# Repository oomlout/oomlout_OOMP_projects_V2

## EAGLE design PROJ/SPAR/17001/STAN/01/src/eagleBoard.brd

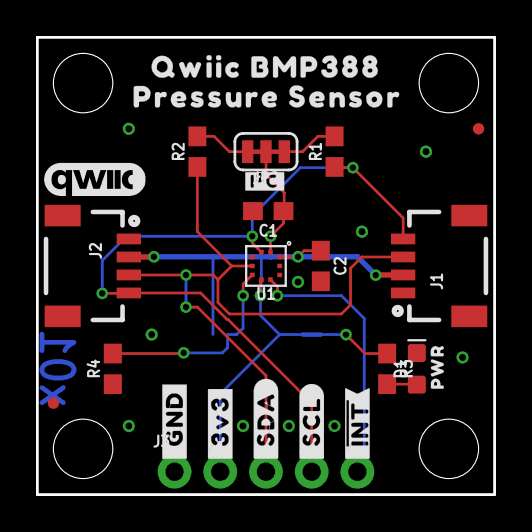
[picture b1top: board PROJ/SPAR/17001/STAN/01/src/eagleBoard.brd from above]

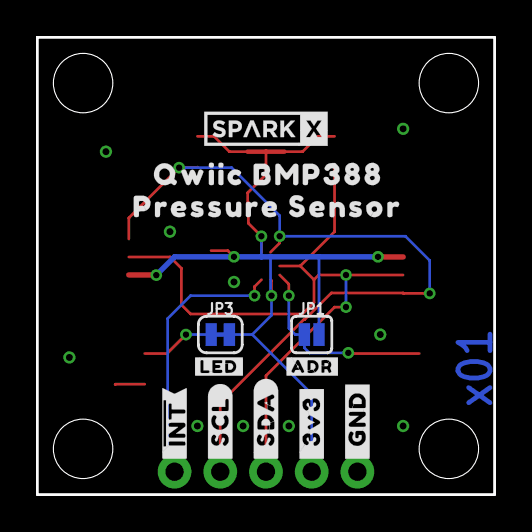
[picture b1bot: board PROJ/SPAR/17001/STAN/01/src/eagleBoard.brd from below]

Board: 2 copper layers, 25.4 x 25.4 mm, 38 parts (12 on the bottom side), 10 nets.

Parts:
A1: QWIIC_BOARD_OUTLINEH; QWIIC_BOARD_MOUNT_HOLES
C1, C2: 0.1uF; 0603
D1: RED; LED-0603
FD1, FD2: FIDUCIALUFIDUCIAL; FIDUCIAL-MICRO
FRAME1: FRAME-LETTERNO_PACKAGE; DUMMY
J1, J2: 1X04_1MM_RA
J3: 1X05_NO_SILK
JP1: SMT-JUMPER_2_NO_SILK
JP2: SMT-JUMPER_3_2-NC_TRACE_SILK
JP3: SMT-JUMPER_2_NC_TRACE_SILK
R1, R2: 2.2k; 0603
R3: 1k; 0603
R4: 10k; 0603
U1: BMP388BMP388; LGA-10(2X2)
U$1, U$13: #_GND#3889
U$2, U$12: #_3V3#3890
U$3, U$11: #_SDA#3891
U$4, U$10: #_SCL#3892
U$5, U$9: #_#INT##3893
U$6: #I�C#1
U$7: #ADR#2
U$8: #LED#0
U$14, U$17: QWIIC_BMP3888
U$15, U$18: PRESSURE_SENSOR9
U$16: QWIIC_COPYRIGHT_SMALL
U$19: SPARKX-SMALL
U$20: PWR0

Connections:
3.3V: C1.1, C2.1, J1.2, J2.2, J3.2, JP1.2, JP2.2, JP3.2, U1.1, U1.6, U1.10
ADR: JP1.1, R4.2, U1.5
GND: C1.2, C2.2, D1.C, J1.1, J2.1, J3.1, R4.1, U1.3, U1.8, U1.9
INT: J3.5, U1.7
unnamed: JP2.3, R2.2
unnamed: JP2.1, R1.2
unnamed: JP3.1, R3.1
unnamed: D1.A, R3.2
SCL: J1.4, J2.4, J3.4, R1.1, U1.2
SDA: J1.3, J2.3, J3.3, R2.1, U1.4

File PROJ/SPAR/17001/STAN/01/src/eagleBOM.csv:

"Part";"Value";"Device";"Package";"Description";"DESIGNER";"PROD_ID";"VALUE";"VERSION";
"A1";"QWIIC_BOARD_OUTLINEH";"QWIIC_BOARD_OUTLINEH";"QWIIC_BOARD_MOUNT_HOLES";"Standard Outline of a Qwiic Board. Good for defining a spot on shields and board areas in which to mount a Qwiic Board.";"";"";"";"";
"C1";"0.1uF";"0.1UF-0603-25V-(+80/-20%)";"0603";"0.1µF ceramic capacitors";"";"CAP-00810";"0.1uF";"";
"C2";"0.1uF";"0.1UF-0603-25V-(+80/-20%)";"0603";"0.1µF ceramic capacitors";"";"CAP-00810";"0.1uF";"";
"D1";"RED";"LED-RED0603";"LED-0603";"Red SMD LED";"";"DIO-00819";"RED";"";
"FD1";"FIDUCIALUFIDUCIAL";"FIDUCIALUFIDUCIAL";"FIDUCIAL-MICRO";"Fiducial Alignment Points";"";"";"";"";
"FD2";"FIDUCIALUFIDUCIAL";"FIDUCIALUFIDUCIAL";"FIDUCIAL-MICRO";"Fiducial Alignment Points";"";"";"";"";
"FRAME1";"FRAME-LETTERNO_PACKAGE";"FRAME-LETTERNO_PACKAGE";"DUMMY";"Schematic Frame - Letter";"Nobody";"";"";"v01";
"J1";"";"QWIIC_CONNECTORJS-1MM";"1X04_1MM_RA";"SparkFun I2C Standard Qwiic Connector";"";"";"";"";
"J2";"";"QWIIC_CONNECTORJS-1MM";"1X04_1MM_RA";"SparkFun I2C Standard Qwiic Connector";"";"";"";"";
"J3";"";"CONN_05NO_SILK";"1X05_NO_SILK";"Multi connection point. Often used as Generic Header-pin footprint for 0.1 inch spaced/style header connections";"";"";"";"";
"JP1";"";"JUMPER-SMT_2_NO_SILK";"SMT-JUMPER_2_NO_SILK";"Normally open jumper";"";"";"";"";
"JP2";"";"JUMPER-SMT_3_2-NC_TRACE_SILK";"SMT-JUMPER_3_2-NC_TRACE_SILK";"Normally closed trace jumper (2 of 2 connections)";"";"";"";"";
"JP3";"";"JUMPER-SMT_2_NC_TRACE_SILK";"SMT-JUMPER_2_NC_TRACE_SILK";"Normally closed trace jumper";"";"";"";"";
"R1";"2.2k";"2.2KOHM-0603-1/10W-1%";"0603";"2.2kΩ resistor";"";"RES-08272";"2.2k";"";
"R2";"2.2k";"2.2KOHM-0603-1/10W-1%";"0603";"2.2kΩ resistor";"";"RES-08272";"2.2k";"";
"R3";"1k";"1KOHM-0603-1/10W-1%";"0603";"1kΩ resistor";"";"RES-07856";"1k";"";
"R4";"10k";"10KOHM-0603-1/10W-1%";"0603";"10kΩ resistor";"";"RES-00824";"10k";"";
"U1";"BMP388BMP388";"BMP388BMP388";"LGA-10(2X2)";"Bosch BMP3388 Pressure Sensor";"";"IC-14045";"";"";

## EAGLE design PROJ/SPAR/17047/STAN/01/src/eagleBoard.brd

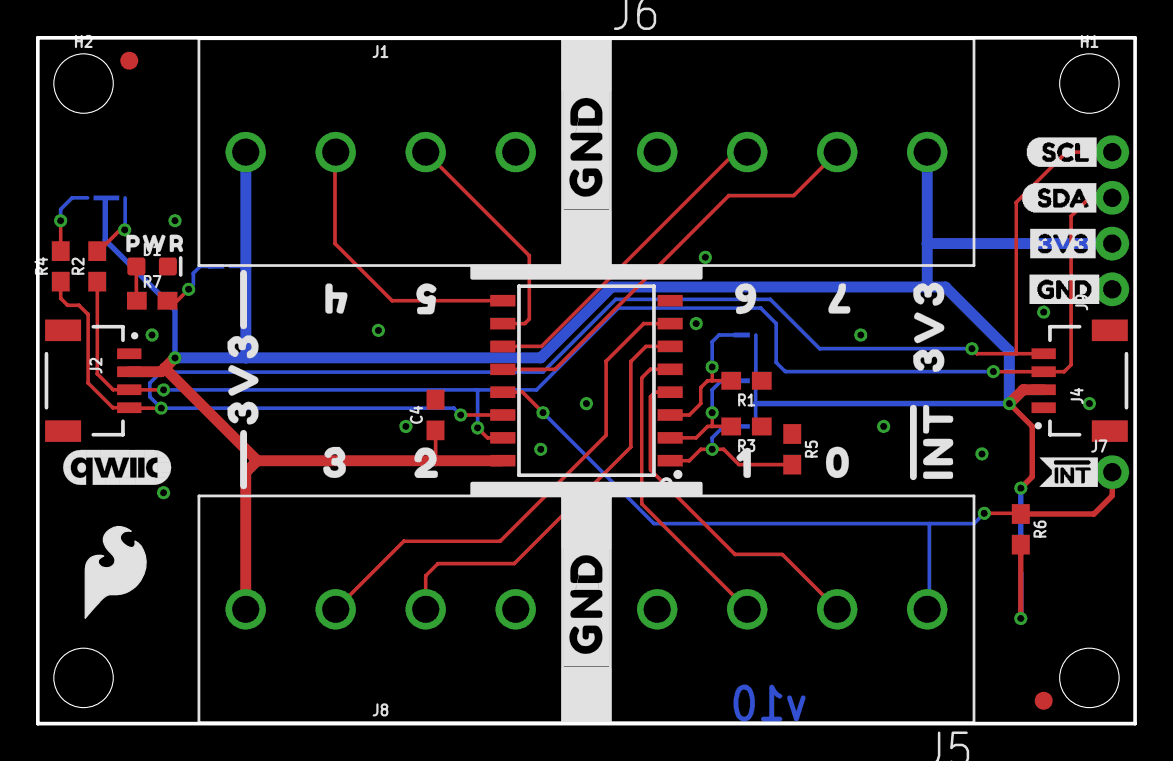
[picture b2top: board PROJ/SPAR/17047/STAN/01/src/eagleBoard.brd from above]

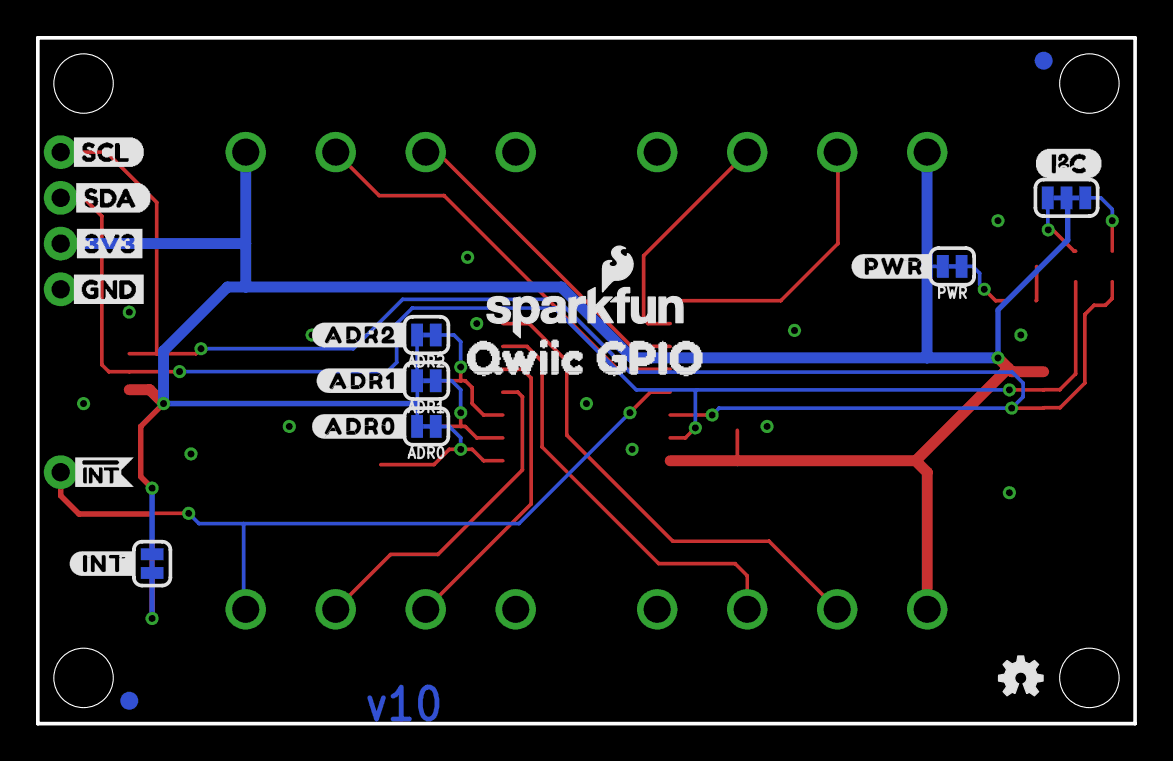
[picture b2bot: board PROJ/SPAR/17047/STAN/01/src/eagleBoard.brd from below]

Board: 2 copper layers, 61.0 x 38.1 mm, 69 parts (22 on the bottom side), 21 nets.

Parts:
ADR0, ADR1, ADR2: JUMPER-SMT_2_NC_TRACE_SILK; SMT-JUMPER_2_NC_TRACE_SILK
C4: 0.1uF; 0603
D1: RED; LED-0603
FD1, FD2: FIDUCIAL1X2; FIDUCIAL-1X2
FRAME1: FRAME-LETTER; CREATIVE_COMMONS
H1, H2: STAND-OFF
I2C: JUMPER-SMT_3_2-NC_TRACE_SILK; SMT-JUMPER_3_2-NC_TRACE_SILK
INT: JUMPER-SMT_2_NC_TRACE_SILK; SMT-JUMPER_2_NC_TRACE_SILK
J1, J5, J6, J8: LATCHTERMINAL-5MM-4
J2, J4: QWIIC; JST04_1MM_RA
J7: 1X01_NO_SILK
J9: 1X04_NO_SILK
JP2, JP6: FIDUCIAL1X2; FIDUCIAL-1X2
JP3, JP4: STAND-OFF
LOGO1: OSHW-LOGOMINI; OSHW-LOGO-MINI
LOGO2: REVISION
LOGO3: SFE_LOGO_NAME_FLAME.1_INCH; SFE_LOGO_NAME_FLAME_.1
LOGO4: SFE_LOGO_FLAME.2_INCH; SFE_LOGO_FLAME_.2
PWR: JUMPER-SMT_2_NC_TRACE_SILK; SMT-JUMPER_2_NC_TRACE_SILK
R1, R2, R3, R4, R5: 2.2k; 0603
R6: 10k; 0603
R7: 1k; 0603
U3: TCA9534; 16SOIC
U$1: I2C
U$2: 20
U$3, U$26: 3V33
U$4: 30
U$5: #ADR1#0
U$6: 10
U$7, U$25: GND4
U$8: QWIIC_GPIO7
U$9: SCL6
U$10: SDA5
U$11: #ADR2#0
U$12: #INT#0
U$13, U$22, U$29: #INT0
U$14: 00
U$15: #ADR0#0
U$21: QWIIC_6MM
U$23: SCL0
U$24: SDA1
U$30, U$31: 3V30
U$32: 40
U$33: 50
U$34: PWR0
U$35: 60
U$37: 70
U$38, U$40: #GND#0
U$39: #PWR#0

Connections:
3.3V: ADR0.2, ADR1.2, ADR2.2, C4.1, I2C.2, INT.2, J1.1, J2.2, J4.2, J6.4, J8.4, J9.2, PWR.2, U3.16
!INT: J5.1, J7.1, R6.1, U3.13
ADR0: ADR0.1, R5.2, U3.1
ADR1: ADR1.1, R3.2, U3.2
ADR2: ADR2.1, R1.2, U3.3
GND: C4.2, D1.C, J1.4, J2.1, J4.1, J5.4, J6.1, J8.1, J9.1, R1.1, R3.1, R5.1, U3.8
unnamed: INT.1, R6.2
unnamed: D1.A, R7.1
unnamed: PWR.1, R7.2
P0: J5.2, U3.4
P1: J5.3, U3.5
P2: J8.2, U3.6
P3: J8.3, U3.7
P4: J1.2, U3.9
P5: J1.3, U3.10
P6: J6.2, U3.11
P7: J6.3, U3.12
SCL: J2.4, J4.4, J9.4, R4.1, U3.14
SCL_PU1: I2C.1, R2.2
SDA: J2.3, J4.3, J9.3, R2.1, U3.15
SDA_PU1: I2C.3, R4.2

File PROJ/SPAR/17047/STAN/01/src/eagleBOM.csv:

"Part";"Value";"Device";"Package";"Description";"DESIGNER";"PROD_ID";"REV";"STOREFRONT_SKU";"VALUE";
"ADR0";"JUMPER-SMT_2_NC_TRACE_SILK";"JUMPER-SMT_2_NC_TRACE_SILK";"SMT-JUMPER_2_NC_TRACE_SILK";"Normally closed trace jumper";"";"";"";"";"";
"ADR1";"JUMPER-SMT_2_NC_TRACE_SILK";"JUMPER-SMT_2_NC_TRACE_SILK";"SMT-JUMPER_2_NC_TRACE_SILK";"Normally closed trace jumper";"";"";"";"";"";
"ADR2";"JUMPER-SMT_2_NC_TRACE_SILK";"JUMPER-SMT_2_NC_TRACE_SILK";"SMT-JUMPER_2_NC_TRACE_SILK";"Normally closed trace jumper";"";"";"";"";"";
"C4";"0.1uF";"0.1UF-0603-25V-(+80/-20%)";"0603";"0.1µF ceramic capacitors";"";"CAP-00810";"";"";"0.1uF";
"D1";"RED";"LED-RED0603";"LED-0603";"Red SMD LED";"";"DIO-00819";"";"";"RED";
"FD1";"FIDUCIAL1X2";"FIDUCIAL1X2";"FIDUCIAL-1X2";"Fiducial Alignment Points";"";"";"";"";"";
"FD2";"FIDUCIAL1X2";"FIDUCIAL1X2";"FIDUCIAL-1X2";"Fiducial Alignment Points";"";"";"";"";"";
"FRAME1";"FRAME-LETTER";"FRAME-LETTER";"CREATIVE_COMMONS";"Schematic Frame - Letter";"";"";"";"";"";
"H1";"STAND-OFF";"STAND-OFF";"STAND-OFF";"Stand Off";"";"";"";"";"";
"H2";"STAND-OFF";"STAND-OFF";"STAND-OFF";"Stand Off";"";"";"";"";"";
"I2C";"JUMPER-SMT_3_2-NC_TRACE_SILK";"JUMPER-SMT_3_2-NC_TRACE_SILK";"SMT-JUMPER_3_2-NC_TRACE_SILK";"Normally closed trace jumper (2 of 2 connections)";"";"";"";"";"";
"INT";"JUMPER-SMT_2_NC_TRACE_SILK";"JUMPER-SMT_2_NC_TRACE_SILK";"SMT-JUMPER_2_NC_TRACE_SILK";"Normally closed trace jumper";"";"";"";"";"";
"J1";"";"CONN_04LATCH";"LATCHTERMINAL-5MM-4";"Multi connection point. Often used as Generic Header-pin footprint for 0.1 inch spaced/style header connections";"";"CON-14722";"";"PRT-15900";"";
"J2";"QWIIC";"QWIIC_CONNECTORJS-1MM";"JST04_1MM_RA";"SparkFun I2C Standard Qwiic Connector";"";"CONN-13694";"";"";"QWIIC_RIGHT_ANGLE";
"J4";"QWIIC";"QWIIC_CONNECTORJS-1MM";"JST04_1MM_RA";"SparkFun I2C Standard Qwiic Connector";"";"CONN-13694";"";"";"QWIIC_RIGHT_ANGLE";
"J5";"";"CONN_04LATCH";"LATCHTERMINAL-5MM-4";"Multi connection point. Often used as Generic Header-pin footprint for 0.1 inch spaced/style header connections";"";"CON-14722";"";"PRT-15900";"";
"J6";"";"CONN_04LATCH";"LATCHTERMINAL-5MM-4";"Multi connection point. Often used as Generic Header-pin footprint for 0.1 inch spaced/style header connections";"";"CON-14722";"";"PRT-15900";"";
"J7";"";"CONN_01PTH_NO_SILK_YES_STOP";"1X01_NO_SILK";"Single connection point. Often used as Generic Header-pin footprint for 0.1 inch spaced/style header connections";"";"";"";"";"";
"J8";"";"CONN_04LATCH";"LATCHTERMINAL-5MM-4";"Multi connection point. Often used as Generic Header-pin footprint for 0.1 inch spaced/style header connections";"";"CON-14722";"";"PRT-15900";"";
"J9";"";"CONN_041X04_NO_SILK";"1X04_NO_SILK";"Multi connection point. Often used as Generic Header-pin footprint for 0.1 inch spaced/style header connections";"";"CONN-09696";"";"";"";
"JP2";"FIDUCIAL1X2";"FIDUCIAL1X2";"FIDUCIAL-1X2";"Fiducial Alignment Points";"";"";"";"";"";
"JP3";"STAND-OFF";"STAND-OFF";"STAND-OFF";"Stand Off";"";"";"";"";"";
"JP4";"STAND-OFF";"STAND-OFF";"STAND-OFF";"Stand Off";"";"";"";"";"";
"JP6";"FIDUCIAL1X2";"FIDUCIAL1X2";"FIDUCIAL-1X2";"Fiducial Alignment Points";"";"";"";"";"";
"LOGO1";"OSHW-LOGOMINI";"OSHW-LOGOMINI";"OSHW-LOGO-MINI";"Open-Source Hardware (OSHW) Logo";"";"";"";"";"";
"LOGO2";"REVISION";"REVISION";"REVISION";""Revision By" Text";"";"";"";"";"";
"LOGO3";"SFE_LOGO_NAME_FLAME.1_INCH";"SFE_LOGO_NAME_FLAME.1_INCH";"SFE_LOGO_NAME_FLAME_.1";"SparkFun Font Logo w/ Flame";"";"";"";"";"";
"LOGO4";"SFE_LOGO_FLAME.2_INCH";"SFE_LOGO_FLAME.2_INCH";"SFE_LOGO_FLAME_.2";"SparkFun Flame Logo";"";"";"";"";"";
"PWR";"JUMPER-SMT_2_NC_TRACE_SILK";"JUMPER-SMT_2_NC_TRACE_SILK";"SMT-JUMPER_2_NC_TRACE_SILK";"Normally closed trace jumper";"";"";"";"";"";
"R1";"2.2k";"2.2KOHM-0603-1/10W-1%";"0603";"2.2kΩ resistor";"";"RES-08272";"";"";"2.2k";
"R2";"2.2k";"2.2KOHM-0603-1/10W-1%";"0603";"2.2kΩ resistor";"";"RES-08272";"";"";"2.2k";
"R3";"2.2k";"2.2KOHM-0603-1/10W-1%";"0603";"2.2kΩ resistor";"";"RES-08272";"";"";"2.2k";
"R4";"2.2k";"2.2KOHM-0603-1/10W-1%";"0603";"2.2kΩ resistor";"";"RES-08272";"";"";"2.2k";
"R5";"2.2k";"2.2KOHM-0603-1/10W-1%";"0603";"2.2kΩ resistor";"";"RES-08272";"";"";"2.2k";
"R6";"10k";"10KOHM-0603-1/10W-1%";"0603";"10kΩ resistor";"";"RES-00824";"";"";"10k";
"R7";"1k";"1KOHM-0603-1/10W-1%";"0603";"1kΩ resistor";"";"RES-07856";"";"";"1k";
"U3";"TCA9534";"TCA9534U";"16SOIC";"Texas Instruments TCA9534 I2C -> GPIO Expander";"";"IC-14889";"";"";"TCA9534";

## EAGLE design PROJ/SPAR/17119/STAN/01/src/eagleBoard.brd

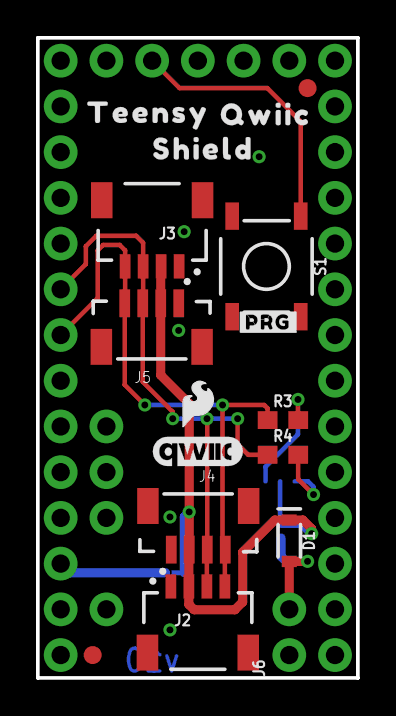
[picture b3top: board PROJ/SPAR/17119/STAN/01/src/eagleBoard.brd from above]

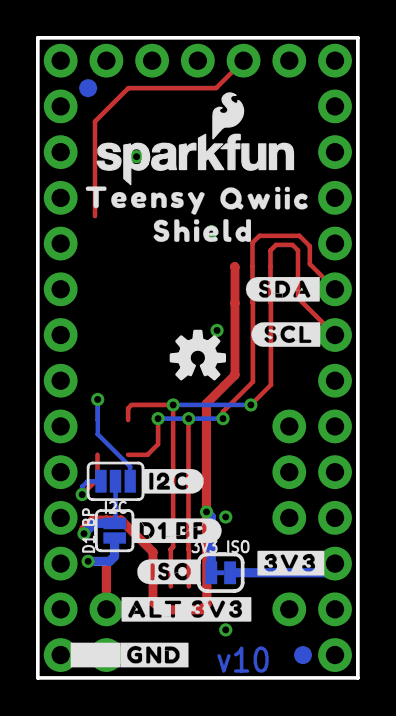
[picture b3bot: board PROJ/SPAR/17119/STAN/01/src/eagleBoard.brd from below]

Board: 2 copper layers, 17.8 x 35.6 mm, 38 parts (18 on the bottom side), 9 nets.

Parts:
3V3_ISO: SMT-JUMPER_2_NC_TRACE_SILK
D1: 3A/10V/280mV; SOD-323
D1_BP: SMT-JUMPER_2_NO_SILK
FD1, FD2, FD3, FD4: FIDUCIAL1X2; FIDUCIAL-1X2
FRAME1: FRAME-LETTER; CREATIVE_COMMONS
I2C: JUMPER-SMT_3_NO_SILK; SMT-JUMPER_3_NO_SILK
J1: TEENSY; TEENSY_NOSILK
J2, J3: QWIIC_RA; JST04_1MM_RA
J4, J5: QWIIC_Vertical; JST04_1MM_VERT
J6: ALT PWR; 1X02_NO_SILK
LOGO1: SFE_LOGO_NAME_FLAME.1_INCH; SFE_LOGO_NAME_FLAME_.1
LOGO2: SFE_LOGO_FLAME.1_INCH; SFE_LOGO_FLAME_.1
LOGO3: OSHW-LOGOS; OSHW-LOGO-S
LOGO4: QWIIC_LOGO_5MM; QWIIC_5MM
R3, R4: 4.7k; 0603
S1: SMD_5.2MM; TACTILE_SWITCH_SMD_5.2MM
U$1: #I2C#0
U$2, U$13: TEENSY0
U$3: 3V36
U$4: #D1_BP#0
U$5: #ALT_3V3#0
U$6: #PRG#0
U$7: #GND#0
U$8, U$12: SHIELD0
U$9, U$11: QWIIC0
U$10: #ISO#0
U$15: #3V3#0
U$18: #SDA#0
U$19: #SCL#0

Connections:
3.3V: 3V3_ISO.1, D1.C, D1_BP.2, I2C.2, J2.2, J3.2, J4.2, J5.2
GND: J1.AGND, J1.GND, J1.GND1, J2.1, J3.1, J4.1, J5.1, J6.1, S1.3
unnamed: I2C.3, R4.2
unnamed: I2C.1, R3.2
unnamed: 3V3_ISO.2, J1.3V
unnamed: D1.A, D1_BP.1, J6.2
unnamed: J1.PROG, S1.1
SCL: J1.19, J2.4, J3.4, J4.4, J5.4, R3.1
SDA: J1.18, J2.3, J3.3, J4.3, J5.3, R4.1

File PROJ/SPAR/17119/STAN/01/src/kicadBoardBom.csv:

"Id";"Designator";"Package";"Quantity";"Designation";"Supplier and ref";
1;"LOGO2";"SFE_LOGO_FLAME_.1";1;"SFE_LOGO_FLAME.1_INCH";;;
2;"J4,J5";"JST04_1MM_VERT";2;"QWIIC_Vertical";;;
3;"U$9,U$11";"QWIIC0";2;"";;;
4;"U$13,U$2";"TEENSY0";2;"";;;
5;"U$6";"#PRG#0";1;"";;;
6;"J1";"TEENSY_NOSILK";1;"TEENSY";;;
7;"FRAME1";"CREATIVE_COMMONS";1;"FRAME-LETTER";;;
8;"R4,R3";"0603";2;"4.7k";;;
9;"U$8,U$12";"SHIELD0";2;"";;;
10;"U$3";"3V36";1;"";;;
11;"D1";"SOD-323";1;"3A/10V/280mV";;;
12;"J3,J2";"JST04_1MM_RA";2;"QWIIC_RA";;;
13;"LOGO4";"QWIIC_5MM";1;"QWIIC_LOGO_5MM";;;
14;"FD3,FD1,FD2,FD4";"FIDUCIAL-1X2";4;"FIDUCIAL1X2";;;
15;"S1";"TACTILE_SWITCH_SMD_5.2MM";1;"SMD_5.2MM";;;
16;"J6";"1X02_NO_SILK";1;"ALT PWR";;;
17;"U$1";"#I2C#0";1;"";;;
18;"UNK3V3_ISO0";"SMT-JUMPER_2_NC_TRACE_SILK";1;"";;;
19;"U$7";"#GND#0";1;"";;;
20;"LOGO3";"OSHW-LOGO-S";1;"OSHW-LOGOS";;;
21;"U$10";"#ISO#0";1;"";;;
22;"D1_BP0";"SMT-JUMPER_2_NO_SILK";1;"";;;
23;"U$15";"#3V3#0";1;"";;;
24;"LOGO1";"SFE_LOGO_NAME_FLAME_.1";1;"SFE_LOGO_NAME_FLAME.1_INCH";;;
25;"U$18";"#SDA#0";1;"";;;
26;"U$5";"#ALT_3V3#0";1;"";;;
27;"U$19";"#SCL#0";1;"";;;
28;"U$4";"#D1_BP#0";1;"";;;
29;"I2C0";"SMT-JUMPER_3_NO_SILK";1;"JUMPER-SMT_3_NO_SILK";;;

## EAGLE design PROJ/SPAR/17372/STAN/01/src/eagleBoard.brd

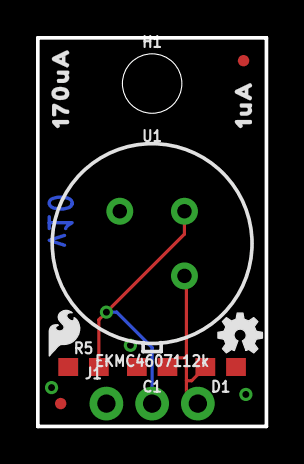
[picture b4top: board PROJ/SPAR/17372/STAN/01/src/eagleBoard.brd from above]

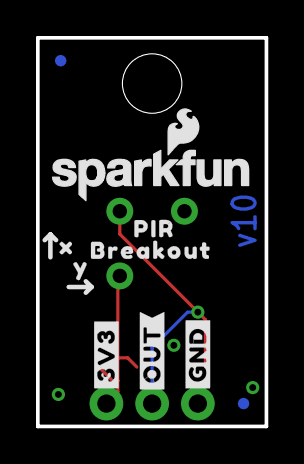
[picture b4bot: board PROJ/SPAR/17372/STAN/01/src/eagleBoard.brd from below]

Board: 2 copper layers, 12.7 x 21.6 mm, 23 parts (10 on the bottom side), 3 nets.

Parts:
C1: 0.1uF; 0603
D1: 24V; 0603
FRAME1: FRAME-LETTER; CREATIVE_COMMONS
H1: STAND-OFF
J1: 1X03_NO_SILK
JP2, JP6, JP8, JP9: FIDUCIALUFIDUCIAL; MICRO-FIDUCIAL
LOGO1: OSHW-LOGOMINI; OSHW-LOGO-MINI
LOGO3: SFE_LOGO_NAME_FLAME.1_INCH; SFE_LOGO_NAME_FLAME_.1
LOGO4: SFE_LOGO_FLAME.1_INCH; SFE_LOGO_FLAME_.1
R5: 47k; 0603
U1: EKMC4607112k; TO-3
U$1: #3V3#0
U$2: 170UA0
U$3: #GND#0
U$9: 1UA0
U$11: #OUT#0
U$12: BREAKOUT0
U$13: PIR0
U$14: X0
U$16: Y0

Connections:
3.3V: C1.1, D1.2, J1.3, U1.VDD
GND: C1.2, D1.1, J1.1, R5.1, U1.GND
PIR_OUT: J1.2, R5.2, U1.OUT

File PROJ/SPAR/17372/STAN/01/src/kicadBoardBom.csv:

"Id";"Designator";"Package";"Quantity";"Designation";"Supplier and ref";
1;"FRAME1";"CREATIVE_COMMONS";1;"FRAME-LETTER";;;
2;"R5";"0603";1;"47k";;;
3;"U$2";"170UA0";1;"";;;
4;"U$9";"1UA0";1;"";;;
5;"LOGO1";"OSHW-LOGO-MINI";1;"OSHW-LOGOMINI";;;
6;"U1";"TO-3";1;"EKMC4607112k";;;
7;"H1";"STAND-OFF";1;"STAND-OFF";;;
8;"J1";"1X03_NO_SILK";1;"";;;
9;"D1";"0603";1;"24V";;;
10;"LOGO4";"SFE_LOGO_FLAME_.1";1;"SFE_LOGO_FLAME.1_INCH";;;
11;"JP9,JP8,JP2,JP6";"MICRO-FIDUCIAL";4;"FIDUCIALUFIDUCIAL";;;
12;"C1";"0603";1;"0.1uF";;;
13;"U$11";"#OUT#0";1;"";;;
14;"U$3";"#GND#0";1;"";;;
15;"LOGO3";"SFE_LOGO_NAME_FLAME_.1";1;"SFE_LOGO_NAME_FLAME.1_INCH";;;
16;"U$12";"BREAKOUT0";1;"";;;
17;"U$13";"PIR0";1;"";;;
18;"U$1";"#3V3#0";1;"";;;
19;"U$16";"Y0";1;"";;;
20;"U$14";"X0";1;"";;;

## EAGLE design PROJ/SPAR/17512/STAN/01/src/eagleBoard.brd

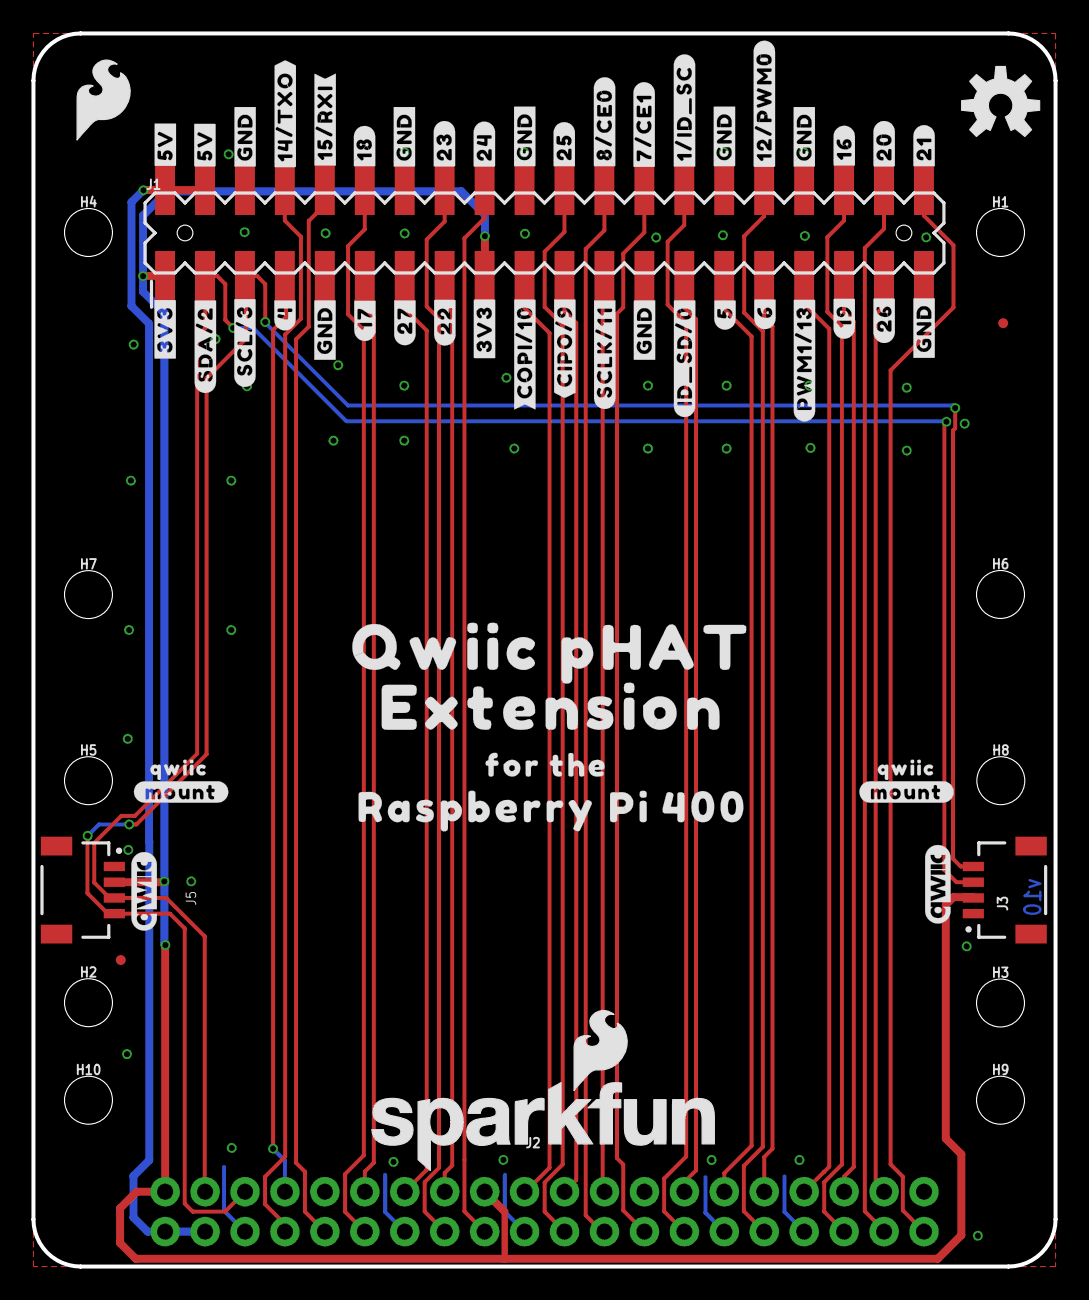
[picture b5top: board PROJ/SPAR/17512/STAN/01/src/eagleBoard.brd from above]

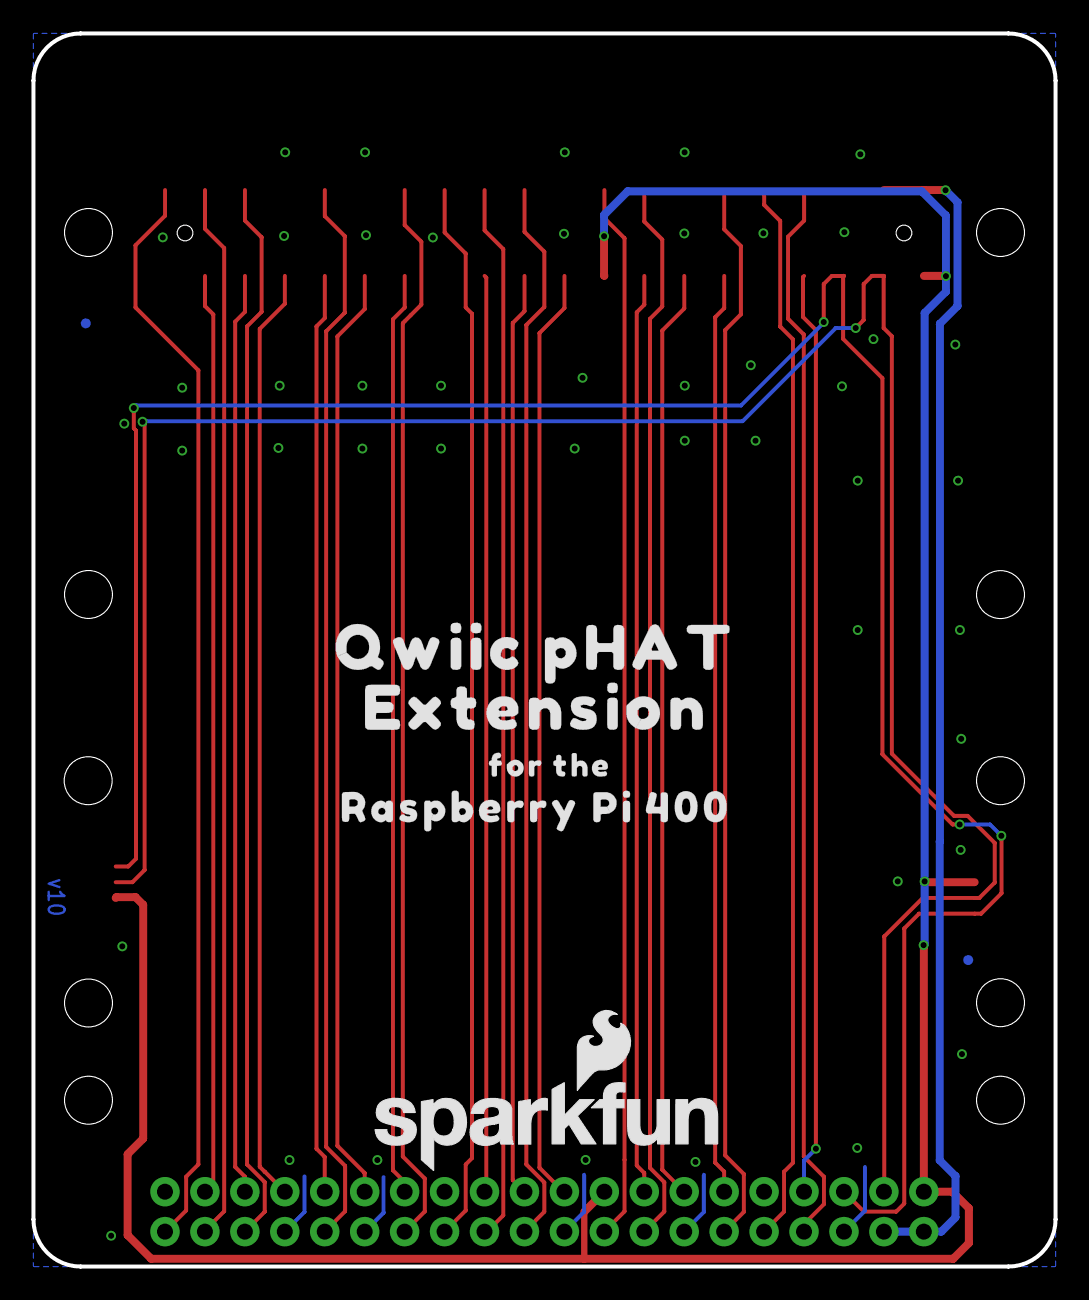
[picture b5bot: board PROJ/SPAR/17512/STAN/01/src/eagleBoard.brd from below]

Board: 2 copper layers, 65.0 x 78.4 mm, 77 parts (7 on the bottom side), 31 nets.

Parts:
FD1, FD2, FD3, FD4: FIDUCIALUFIDUCIAL; FIDUCIAL-MICRO
FRAME1: FRAME-LETTER; CREATIVE_COMMONS
H1, H2, H3, H4, H5, H6, H7, H8, H9, H10: STAND-OFFTIGHT; STAND-OFF-TIGHT
J1: RASPBERRYPI-40-PIN-GPIO_SMD_MALE; RASPBERRY_PI_HAT_40_PIN_SMD_MALE
J2: RASPBERRYPI-40-PIN-GPIO_RIGHT_ANGLE; 2X20_RIGHT_ANGLE
J3, J5: QWIIC_RIGHT_ANGLE; JST04_1MM_RA
LOGO1, LOGO4: QWIIC_LOGO_5MM; QWIIC_5MM
LOGO2, LOGO5: SFE_LOGO_NAME_FLAME.2_INCH; SFE_LOGO_NAME_FLAME_.2
LOGO3: OSHW-LOGOM; OSHW-LOGO-M
U$1: #SDA#2#4
U$2: #SCL#3#4
U$3, U$13: FOR_THE40034
U$4, U$5: #3V3#0
U$6: #4#4
U$7: #5#28
U$8, U$9: #5V#28
U$10: #6#28
U$11: #7#CE1#29
U$12: #8#CE0#29
U$14: #SCLK#11#28
U$15: #ID_SD#0#28
U$16: #12#PWM0#29
U$17: #PWM1#13#28
U$18: #14#TXO#29
U$19: #15#RXI#29
U$20: #16#29
U$21: #17#5
U$22: #18#29
U$23: #19#28
U$24: #20#29
U$25: #21#29
U$26: #22#28
U$27: #23#29
U$28: #24#29
U$29: #25#29
U$30: #26#28
U$31: #27#18
U$32, U$33, U$34, U$35, U$36, U$37, U$38, U$39: #GND#28
U$40: #1#ID_SC#29
U$51: #CIPO#9#28
U$52: #COPI#10#28
U$75, U$89: QWIIC_PHAT31
U$76, U$90: EXTENSION32
U$81: SFE_LOGO_FLAME_.2
U$82, U$83: #MOUNT#29
U$84, U$85: QWIIC30
U$86, U$91: RASPBERRY_PI_40033

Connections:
0/ID_SD: J1.27, J2.27
1/ID_SC: J1.28, J2.28
2/SDA: J1.3, J2.3, J3.3, J5.3
3.3V: J1.1, J1.17, J2.1, J2.17, J3.2, J5.2
3/SCL: J1.5, J2.5, J3.4, J5.4
5V: J1.2, J1.4, J2.2, J2.4
7/CE1: J1.26, J2.26
8/CE0: J1.24, J2.24
9/CIPO: J1.21, J2.21
10/COPI: J1.19, J2.19
11/SCLK: J1.23, J2.23
12/PWM0: J1.32, J2.32
13/PWM1: J1.33, J2.33
14/TXO: J1.8, J2.8
15/RXI: J1.10, J2.10
18/PCM_CLK: J1.12, J2.12
19/PCM_FS: J1.35, J2.35
20/PCM_DIN: J1.38, J2.38
21/PCM_DOUT: J1.40, J2.40
GND: J1.6, J1.9, J1.14, J1.20, J1.25, J1.30, J1.34, J1.39, J2.6, J2.9, J2.14, J2.20, J2.25, J2.30, J2.34, J2.39, J3.1, J5.1
GP4: J1.7, J2.7
GP5: J1.29, J2.29
GP6: J1.31, J2.31
GP16: J1.36, J2.36
GP17: J1.11, J2.11
GP22: J1.15, J2.15
GP23: J1.16, J2.16
GP24: J1.18, J2.18
GP25: J1.22, J2.22
GP26: J1.37, J2.37
GP27: J1.13, J2.13

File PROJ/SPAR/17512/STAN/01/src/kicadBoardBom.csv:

"Id";"Designator";"Package";"Quantity";"Designation";"Supplier and ref";
1;"U$10";"#6#28";1;"";;;
2;"U$35,U$33,U$34,U$37,U$39,U$38,U$36,U$32";"#GND#28";8;"";;;
3;"U$82,U$83";"#MOUNT#29";2;"";;;
4;"J2";"2X20_RIGHT_ANGLE";1;"RASPBERRYPI-40-PIN-GPIO_RIGHT_ANGLE";;;
5;"H9,H4,H6,H1,H10,H3,H7,H5,H2,H8";"STAND-OFF-TIGHT";10;"STAND-OFFTIGHT";;;
6;"U$27";"#23#29";1;"";;;
7;"LOGO2,LOGO5";"SFE_LOGO_NAME_FLAME_.2";2;"SFE_LOGO_NAME_FLAME.2_INCH";;;
8;"U$16";"#12#PWM0#29";1;"";;;
9;"U$6";"#4#4";1;"";;;
10;"U$7";"#5#28";1;"";;;
11;"U$52";"#COPI#10#28";1;"";;;
12;"U$1";"#SDA#2#4";1;"";;;
13;"U$23";"#19#28";1;"";;;
14;"U$4,U$5";"#3V3#0";2;"";;;
15;"U$20";"#16#29";1;"";;;
16;"U$2";"#SCL#3#4";1;"";;;
17;"U$12";"#8#CE0#29";1;"";;;
18;"FRAME1";"CREATIVE_COMMONS";1;"FRAME-LETTER";;;
19;"U$8,U$9";"#5V#28";2;"";;;
20;"LOGO3";"OSHW-LOGO-M";1;"OSHW-LOGOM";;;
21;"U$81";"SFE_LOGO_FLAME_.2";1;"";;;
22;"U$22";"#18#29";1;"";;;
23;"U$85,U$84";"QWIIC30";2;"";;;
24;"U$51";"#CIPO#9#28";1;"";;;
25;"U$75,U$89";"QWIIC_PHAT31";2;"";;;
26;"U$86,U$91";"RASPBERRY_PI_40033";2;"";;;
27;"U$21";"#17#5";1;"";;;
28;"J5,J3";"JST04_1MM_RA";2;"QWIIC_RIGHT_ANGLE";;;
29;"FD1,FD2,FD3,FD4";"FIDUCIAL-MICRO";4;"FIDUCIALUFIDUCIAL";;;
30;"U$25";"#21#29";1;"";;;
31;"J1";"RASPBERRY_PI_HAT_40_PIN_SMD_MALE";1;"RASPBERRYPI-40-PIN-GPIO_SMD_MALE";;;
32;"U$76,U$90";"EXTENSION32";2;"";;;
33;"U$15";"#ID_SD#0#28";1;"";;;
34;"LOGO1,LOGO4";"QWIIC_5MM";2;"QWIIC_LOGO_5MM";;;
35;"U$11";"#7#CE1#29";1;"";;;
36;"U$26";"#22#28";1;"";;;
37;"U$3,U$13";"FOR_THE40034";2;"";;;
38;"U$40";"#1#ID_SC#29";1;"";;;
39;"U$24";"#20#29";1;"";;;
40;"U$19";"#15#RXI#29";1;"";;;
41;"U$30";"#26#28";1;"";;;
42;"U$14";"#SCLK#11#28";1;"";;;
43;"U$29";"#25#29";1;"";;;
44;"U$18";"#14#TXO#29";1;"";;;
45;"U$31";"#27#18";1;"";;;
46;"U$28";"#24#29";1;"";;;
47;"U$17";"#PWM1#13#28";1;"";;;

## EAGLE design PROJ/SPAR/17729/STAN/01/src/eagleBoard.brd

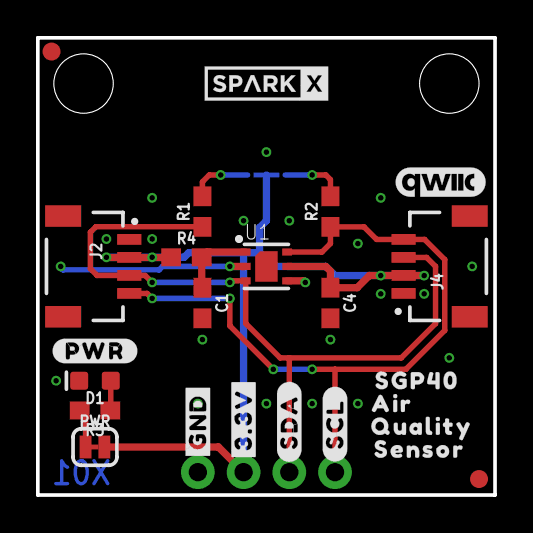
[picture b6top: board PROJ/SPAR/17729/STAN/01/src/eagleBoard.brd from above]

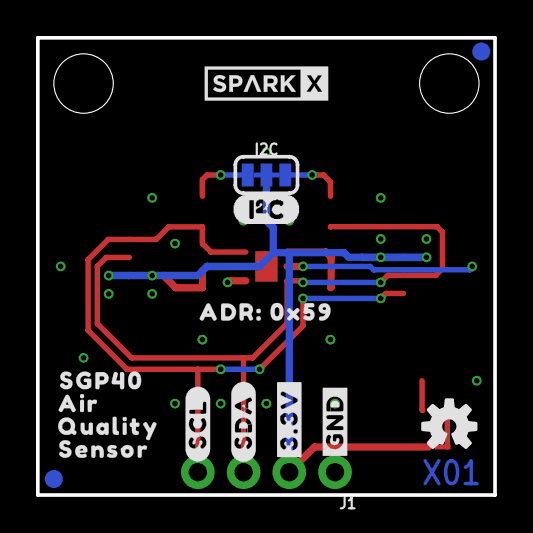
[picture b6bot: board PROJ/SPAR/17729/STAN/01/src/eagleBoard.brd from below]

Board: 2 copper layers, 25.4 x 25.4 mm, 44 parts (16 on the bottom side), 9 nets.

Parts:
C1, C4: 1.0uF; 0603
D1: RED; LED-0603
FRAME1: FRAME-LETTER; CREATIVE_COMMONS
I2C: JUMPER-SMT_3_2-NC_TRACE_SILK; SMT-JUMPER_3_2-NC_TRACE_SILK
J1: 1X04_NO_SILK
J2, J4: QWIIC_RIGHT_ANGLE; JST04_1MM_RA
JP1, JP2, JP5, JP6: FIDUCIAL1X2; FIDUCIAL-1X2
JP3, JP4: STAND-OFF
LOGO1: SPECIAL_INSTRUCTIONS-ORDERING; ORDERING_INSTRUCTIONS
LOGO5: OSHW-LOGOS; OSHW-LOGO-S
PWR: JUMPER-SMT_2_NC_TRACE_SILK; SMT-JUMPER_2_NC_TRACE_SILK
R1, R2: 10k; 0603
R3: 1k; 0603
R4: 4.7; 0603
U1: SGP40
U$1, U$33: #GND#0
U$2, U$34: #3#3V#0
U$3, U$35: #SDA#0
U$4, U$36: #SCL#0
U$10, U$18: SPARKX-LOGO3; SPARKX-SMALL
U$15: I2C
U$16: QWIIC_5MM
U$19, U$20: SGP400
U$23, U$24: AIR0
U$25, U$28: QUALITY0
U$29, U$30: SENSOR0
U$31: ADR#_0X590
U$32: #PWR#0

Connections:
3.3V: C4.1, I2C.2, J1.2, J2.2, J4.2, PWR.2, R4.1, U1.5
GND: C1.2, C4.2, D1.C, J1.1, J2.1, J4.1, U1.2, U1.4, U1.DIEPAD
unnamed: PWR.1, R3.2
unnamed: I2C.3, R1.2
unnamed: D1.A, R3.1
unnamed: I2C.1, R2.2
unnamed: C1.1, R4.2, U1.1
SCL: J1.4, J2.4, J4.4, R2.1, U1.6
SDA: J1.3, J2.3, J4.3, R1.1, U1.3

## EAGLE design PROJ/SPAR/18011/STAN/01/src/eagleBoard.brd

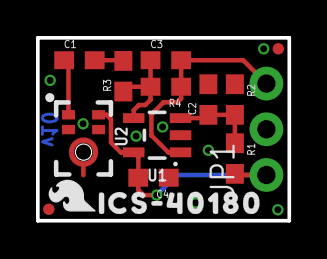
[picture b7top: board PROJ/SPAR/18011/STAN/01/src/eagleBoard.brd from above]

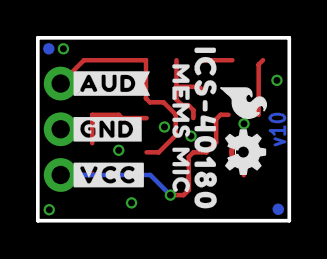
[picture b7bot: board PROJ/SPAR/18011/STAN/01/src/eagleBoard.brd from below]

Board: 2 copper layers, 14.0 x 10.2 mm, 25 parts (9 on the bottom side), 7 nets.

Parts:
C1: 4.7uF; 0603
C2: 1.0uF; 0603
C3: 27pF; 0603
C4: 0.1uF; 0603
FD1, FD2, FD3, FD4: FIDUCIALUFIDUCIAL; FIDUCIAL-MICRO
FRAME2: FRAME-LETTER; CREATIVE_COMMONS
JP1: 1X03_NO_SILK
LOGO1, LOGO3: SFE_LOGO_FLAME.1_INCH; SFE_LOGO_FLAME_.1
LOGO2: OSHW-LOGOMINI; OSHW-LOGO-MINI
R1, R2: 10k; 0603
R3: 4.7k; 0603
R4: 300k; 0603
U1: OPA344; SOT23-5
U2: ICS40180
U$1, U$6: ICS#401800
U$2: MEMS_MIC0
U$3: #GND#0
U$4: #VCC#0
U$5: #AUD#0

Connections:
AUD: C3.2, JP1.3, R4.1, U1.1
GND: C2.2, C4.1, JP1.2, R2.1, U1.2, U2.2, U2.3, U2.4
unnamed: C1.1, U2.1
unnamed: C3.1, R3.1, R4.2, U1.4
unnamed: C1.2, R3.2
unnamed: C2.1, R1.1, R2.2, U1.3
VCC: C4.2, JP1.1, R1.2, U1.5, U2.5

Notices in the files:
parts and their libraries:
SparkFun-Capacitors: Licensing: Creative Commons ShareAlike 4.0 International - https://creativecommons.org/licenses/by-sa/4.0
SparkFun-Aesthetics: Released under the Creative Commons Attribution Share-Alike 4.0 License
SparkFun-Aesthetics: https://creativecommons.org/licenses/by-sa/4.0
